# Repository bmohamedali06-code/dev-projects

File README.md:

# Dev Projects

A collection of frontend web development projects focused on core HTML and web development fundamentals.

---

## 🚀 Projects

### 1. Single-Page CV
A clean, responsive, single-page digital resume built using semantic HTML5 and inline CSS.

* **Live Specs & Requirements:** [roadmap.sh - Single Page CV](https://roadmap.sh/projects/single-page-cv)
* **GitHub Repository:** [View Code](https://github.com/bmohamedali06-code/dev-projects)

---

### 2. HTML-Only Portfolio
A developer portfolio built using HTML tables, inline styles, and semantic structural tags to construct a multi-column wireframe layout.

* **Live Specs & Requirements:** [roadmap.sh - Basic HTML Website](https://roadmap.sh/projects/basic-html-website)
* **GitHub Repository:** [View Code](https://github.com/bmohamedali06-code/dev-projects)

---

### 3. Contact Us Form Page
A fully structured, accessible HTML contact form page designed without external CSS frameworks, emphasizing semantic layout alignment, browser form controls, and validation attributes.

* **Live Specs & Requirements:** [roadmap.sh - Contact Form](https://roadmap.sh/projects/contact-form))
* **GitHub Repository:** [View Code](https://github.com/bmohamedali06-code/dev-projects)

#### Key Highlights & Features:
- **Semantic Form Components:** Structured using native `<form>`, `<label>`, `<fieldset>`, `<legend>`, `<select>`, and `<textarea>` elements.
- **Native Browser Validation:** Configured client-side form rules using `required`, `type="email"`, and `minlength` attributes without relying on JavaScript.
- **HTML Table Alignment:** Form controls, dropdowns, and textareas are aligned precisely across columns using standard table layout geometry (`width="400"`, `cellpadding="8"`, and `box-sizing: border-box`).
- **Accessible Design:** Paired all controls using `for` and `id` attributes to ensure keyboard and screen-reader usability.
## 🛠️ Built With

- **HTML5:** Semantic document tags, tables, and SEO metadata
- **CSS3:** Core inline styles for layout boundaries and basic formatting

---

## 📂 Project Structure

```text
dev-projects/
└── projects/
    ├── single-page-cv/
    └── html-portfolio/

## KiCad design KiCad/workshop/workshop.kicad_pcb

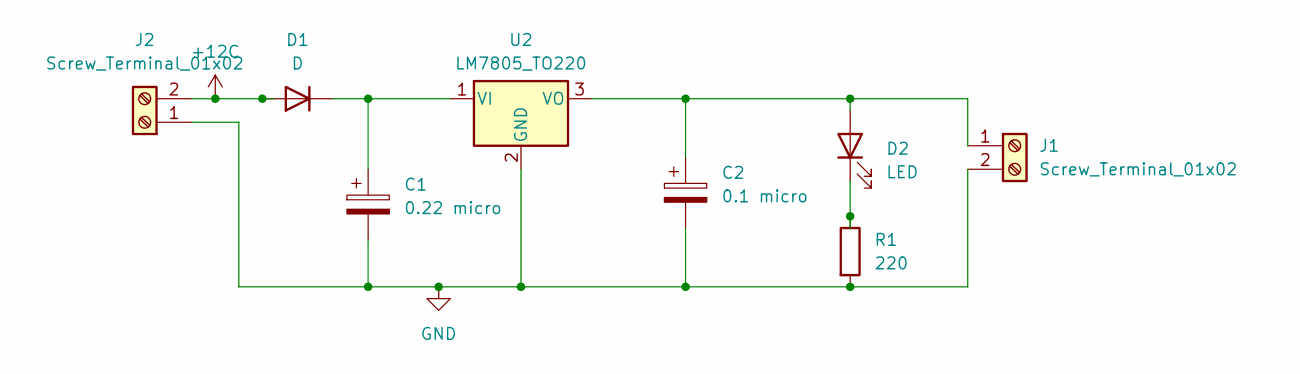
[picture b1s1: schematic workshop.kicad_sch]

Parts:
C1: 0.22 micro; CP_Radial_D5.0mm_P2.50mm
C2: 0.1 micro; CP_Radial_D5.0mm_P2.50mm
D1: D; D_A-405_P12.70mm_Horizontal
D2: LED; LED_D3.0mm
J1, J2: Screw_Terminal_01x02; TerminalBlock_MaiXu_MX126-5.0-02P_1x02_P5.00mm
R1: 220; R_Axial_DIN0207_L6.3mm_D2.5mm_P15.24mm_Horizontal
U2: LM7805_TO220; TO-220-3_Vertical

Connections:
+12C: D1.2 (A), J2.2
GND: C1.2, C2.2, J1.2, J2.1, R1.2, U2.2 (GND)
unnamed: C1.1, D1.1 (K), U2.1 (VI)
unnamed: C2.1, D2.2 (A), J1.1, U2.3 (VO)
unnamed: D2.1 (K), R1.1

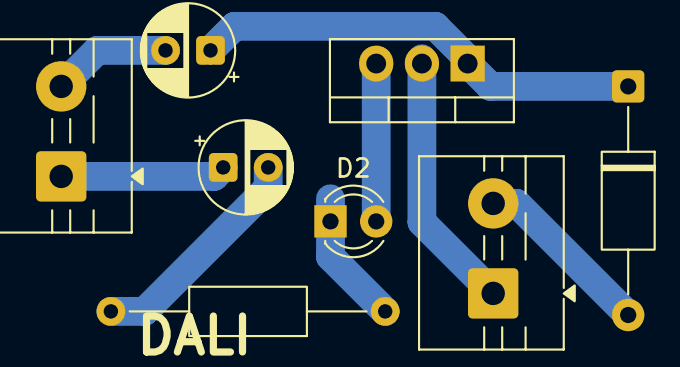
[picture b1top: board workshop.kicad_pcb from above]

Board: 2 copper layers, 8 parts (0 on the bottom side), 5 nets.
